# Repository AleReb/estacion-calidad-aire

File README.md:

# Estación Multiparamétrica de Calidad del Aire

La estación integra sensores **electroquímicos**, **ópticos** y **meteorológicos** en una estructura vertical compacta. El sistema recolecta, almacena y transmite datos **en tiempo casi real**, lo que permite correlacionar calidad del aire y condiciones meteorológicas. Actualmente se encuentra en construcción con pruebas de campo; todos los sensores cuentan con especificaciones validadas y se calibran antes de entrar en operación.

## Características destacadas
- Soporte tipo torre de 2–5 m con exposición 360° y altura de medición a 1,5 m sobre nivel del suelo.
- Alimentación autónoma mediante panel solar y banco de baterías.
- Comunicaciones GSM/4G complementadas con almacenamiento local en microSD.
- Plataforma única con sensores sincronizados y módulos accesibles para reemplazo rápido.
- Incluye colectores para muestreo pasivo de material particulado sedimentable (conforme a Resolución Exenta N° 1449 del MMA, 2023).

## Sensores integrados
| Tipo | Modelo | Rango / Límite | Precisión / Resolución | Tecnología |
| --- | --- | --- | --- | --- |
| PM1.0/2.5/10 | Plantower PMS5003ST | 1 µg/m³ (límite) | ±1 µg/m³ | Óptico láser |
| O₃ | Alphasense OX-B431 | 1 ppb (límite) | ±1 ppbv | Amperométrico |
| NO₂ | Alphasense NO2-B43F | 1 ppb (límite) | ±1 ppbv | Amperométrico |
| CO | Alphasense CO-B4 | 1 ppm (límite) | ±1 ppmv | Amperométrico |
| NO | Alphasense NO-B4 | 1 ppb (límite) | ±1 ppbv | Amperométrico |
| CO₂ | Winsen MH-Z19B/MH-Z19C | 1 ppm (resolución) | — | Infrarrojo NDIR |
| VOC (totales) | Winsen ZE40A-TVOC | 0–2 ppm | 0.01 ppm | PID/MOS |
| SO₂ | Alphasense SO2-B4 (objetivo) | 5 ppb (error) | — | Electroquímico |
| Meteo (T, HR, P, VV, DV, precipitación, radiación, UV, luz) | ComWinTop CWT-UWD-SDTHAPSIR / CWT-UR-S | Según ficha | Ver ficha | RS485 (Modbus) |

## Aplicaciones
- Monitoreo ciudadano y municipal.
- Validación de sensores de bajo costo.
- Correlación con estaciones de referencia.
- Evaluación de impactos urbanos o industriales.

## Guía rápida del repositorio
- `01-requisitos-interesados/`: necesidades y casos de uso basados en el brochure técnico.
- `02-requisitos-sistema/`: requisitos funcionales/no funcionales y especificaciones (contaminantes, soporte meteo, emergentes).
- `03-diseño-arquitectura/`: decisiones, vistas de arquitectura y espacio para diagramas.
- `04-diseño-detallado/`: definición preliminar de hardware, firmware y gestión de datos.
- `05-implementacion/`: árbol para hardware (PCB, carcasas, componentes), firmware (PlatformIO) y software (backend/frontend/scripts).
- `06-10/`: integración, verificación, validación, despliegue y operación/mantenimiento.
- `documentacion/`, `datos/`, `herramientas/`, `configuracion/`: repositorios para datasheets, datasets EPA/WMO, utilidades y perfiles de configuración.
- `gestion-proyecto/planificacion/roles-responsabilidades.md`: lista actualizada de cargos, incluyendo QA/QC y administración de datos.

## Índice de informes y manuales
| Recurso | Ubicación | Descripción |
| --- | --- | --- |
| Manual ISB/AFE y notas de aplicación Alphasense | [`documentacion/datasheets-sensores/sensores-gases/electroquimicos/alphasense/`](documentacion/datasheets-sensores/sensores-gases/electroquimicos/alphasense/) | PDFs AAN-803-05, manual ISB y guía rápida de placas que convierten corriente a voltaje para sensores B4/B43F. |
| Tutorial offsets WEe/AEe | [`documentacion/manuales-tecnicos/calibracion/tutorial-offsets-wee-aee.md`](documentacion/manuales-tecnicos/calibracion/tutorial-offsets-wee-aee.md) | Procedimiento paso a paso para medir offsets electrónicos en placas ISB/AFE con multímetro. |
| Nota técnica AAN-803-05 | [`documentacion/manuales-tecnicos/calibracion/AAN-803-05.pdf`](documentacion/manuales-tecnicos/calibracion/AAN-803-05.pdf) | Referencia oficial del fabricante para calibraciones electroquímicas. |
| Brochure y ficha de operación en terreno | [`documentacion/manuales-tecnicos/operacion/brochure.pdf`](documentacion/manuales-tecnicos/operacion/brochure.pdf) · [`documentacion/manuales-tecnicos/operacion/Ficha Terreno AIRE.pdf`](documentacion/manuales-tecnicos/operacion/Ficha%20Terreno%20AIRE.pdf) | Ficha de despliegue en terreno y brochure visual del proyecto. |
| Reporte laboratorio – voltaje circuito abierto ISB | [`documentacion/informes-pruebas/laboratorio/condiciones-controladas/Volt_Circuito_abierto_ISB_alphasense_est05/Voltage_circuito_abierto_alphasense_estacion_5.pdf`](documentacion/informes-pruebas/laboratorio/condiciones-controladas/Volt_Circuito_abierto_ISB_alphasense_est05/Voltage_circuito_abierto_alphasense_estacion_5.pdf) | Informe LaTeX con fotos e instrumental para medición de voltaje en placas ISB. Incluye fuentes `.tex` e imágenes en `img/`. |
| Reporte campo – co-ubicación SINCA | [`documentacion/informes-pruebas/campo/co-ubicacion-sinca/calibracion-sinca-1.pdf`](documentacion/informes-pruebas/campo/co-ubicacion-sinca/calibracion-sinca-1.pdf) | Evidencia PDF de campaña de co-ubicación para calibraciones con red SINCA. |

## Equipo de trabajo
| Rol | Responsable | Función principal |
| --- | --- | --- |
| Dirección del proyecto | Zoe Fleming | Define lineamientos estratégicos, asegura recursos y relación con interesados de alto nivel. |
| Coordinación general | Luis Gómez | Coordina disciplinas, consolida reportes de avance y comunica el estado del proyecto. |
| Firmware y comunicaciones | Alejandro Rebolledo | Lidera programación de firmware, integración de sensores y enlaces GSM/4G/RS485. |
| Operaciones en terreno | Pablo Ortiz | Gestiona despliegues de torres, logística de instalación y soporte en campo. |
| Mediciones y administración de datos | Catalina Azola | Define rutinas de muestreo, resguarda datos de mediciones y entrega datasets a QA/QC. |
| Documentación regulatoria, QA/QC y bases de datos | Christopher Silva | Mantiene cumplimiento normativo, verifica calidad de datos y gestiona respaldos/registros. |
| Diseño de hardware y componentes | Rodrigo Ortega | Diseña la estructura física, integra panel solar + baterías y define componentes mecánicos. |
| Diseño electrónico | Sebastián Adonay | Desarrolla la electrónica de adquisición y acondicionamiento para sensores electroquímicos, ópticos y meteorológicos. |

## Cómo colaborar (incluye uso con Codex)
1. Clona este repositorio y revisa el README antes de abrir Codex.
2. Abre una sesión de Codex desde la raíz (`codex run`), y revisa los archivos en `gestion-proyecto/planificacion/` para conocer roles y tareas pendientes.
3. Documenta nuevas decisiones en la carpeta correspondiente (por ejemplo, requisitos → `02-...`, hardware → `04-diseño-detallado/...`).
4. Añade contenidos reales en los documentos vacíos; si no existe información todavía, deja una nota explícita indicando que está pendiente (mantén el estilo usado hasta ahora).
5. Usa `.gitkeep` para conservar directorios vacíos si agregas nuevos subcontenidos.
6. Antes de hacer commit, ejecuta `git status` para revisar qué archivos cambiaste y organiza los mensajes de commit por área (requisitos, arquitectura, firmware, etc.).

## Contacto
Proyecto en desarrollo: **Estación Multiparamétrica de Monitoreo Ambiental**  \
Contacto: [luis.gomez@udd.cl](mailto:luis.gomez@udd.cl)

## Descargo de Responsabilidad

El código y la documentación de este proyecto se ofrecen "tal cual", sin garantías de ningún tipo, expresas o implícitas. El uso de este material es bajo su propio riesgo. Los autores no se hacen responsables de ningún daño o pérdida que pueda surgir de su uso.

## Licencia

Este proyecto está licenciado bajo la **Creative Commons Attribution-NonCommercial 4.0 International (CC BY-NC 4.0)**.

Usted es libre de:
-   **Compartir** — copiar y redistribuir el material en cualquier medio o formato.
-   **Adaptar** — remezclar, transformar y construir sobre el material.

Bajo los siguientes términos:
-   **Atribución** — Debe dar crédito de manera adecuada, proporcionar un enlace a la licencia, e indicar si se han realizado cambios.
-   **NoComercial** — No puede utilizar el material para una finalidad comercial.

Para ver una copia de esta licencia, visite [http://creativecommons.org/licenses/by-nc/4.0/](http://creativecommons.org/licenses/by-nc/4.0/) o consulte el archivo [LICENSE](LICENSE) en este repositorio.

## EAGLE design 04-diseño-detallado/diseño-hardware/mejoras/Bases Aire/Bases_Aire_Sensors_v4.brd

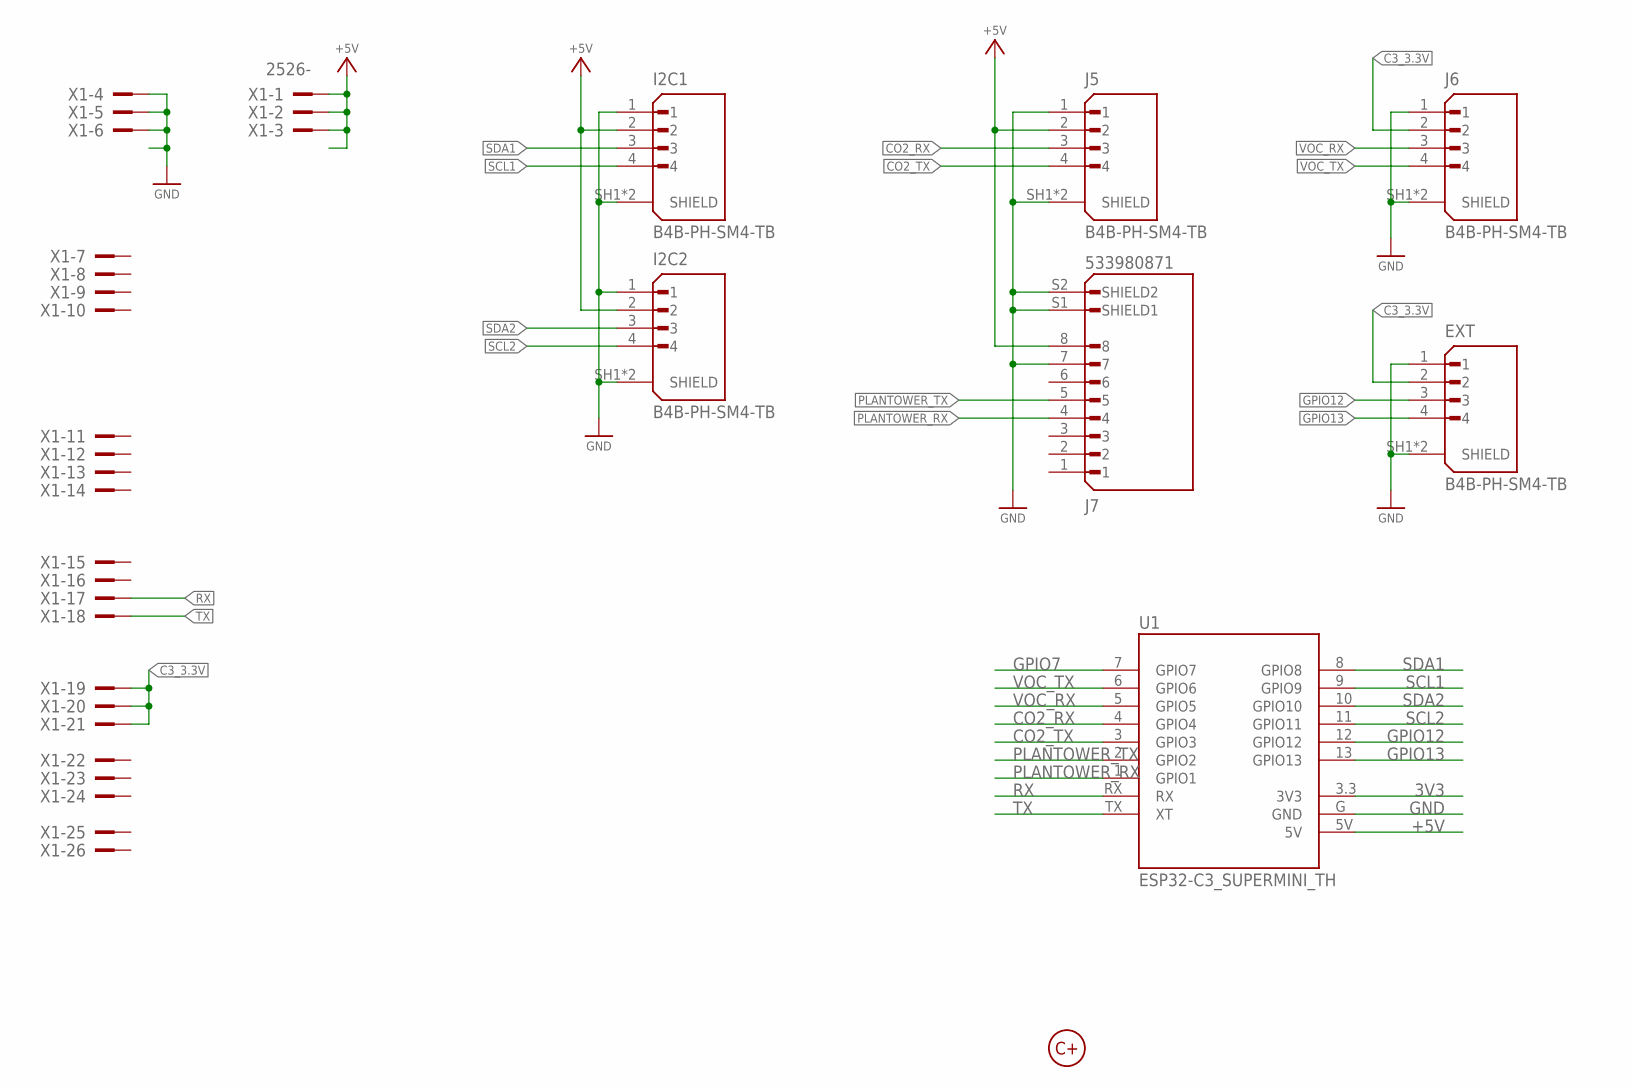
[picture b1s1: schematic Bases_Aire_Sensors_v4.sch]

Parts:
EXT: B4B-PH-SM4-TB; JST_B4B-PH-SM4-TB
I2C1, I2C2: B4B-PH-SM4-TB; JST_B4B-PH-SM4-TB
J5, J6: B4B-PH-SM4-TB; JST_B4B-PH-SM4-TB
J7: 533980871; MOLEX_533980871
U1: ESP32-C3_SUPERMINI_TH; MODULE_ESP32-C3_SUPERMINI_TH
U$1: LOGO_CMAS10MM; LOGO_10MM
X1: 2526-; PAK100/2500-26

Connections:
3V3: U1.3.3 (3V3)
+5V: I2C1.2, I2C2.2, J5.2, J7.8, U1.5V, X1.1, X1.2, X1.3
C3_3.3V: EXT.2, J6.2, X1.19, X1.20, X1.21
CO2_RX: J5.3, U1.4 (GPIO4)
CO2_TX: J5.4, U1.3 (GPIO3)
GND: EXT.1, EXT.SH1 (SHIELD), EXT.SH2 (SHIELD), I2C1.1, I2C1.SH1 (SHIELD), I2C1.SH2 (SHIELD), I2C2.1, I2C2.SH1 (SHIELD), I2C2.SH2 (SHIELD), J5.1, J5.SH1 (SHIELD), J5.SH2 (SHIELD), J6.1, J6.SH1 (SHIELD), J6.SH2 (SHIELD), J7.7, J7.S1 (SHIELD1), J7.S2 (SHIELD2), U1.G (GND), X1.4, X1.5, X1.6
GPIO7: U1.7 (GPIO7)
GPIO12: EXT.3, U1.12 (GPIO12)
GPIO13: EXT.4, U1.13 (GPIO13)
PLANTOWER_RX: J7.4, U1.1 (GPIO1)
PLANTOWER_TX: J7.5, U1.2 (GPIO2)
RX: U1.RX, X1.17
SCL1: I2C1.4, U1.9 (GPIO9)
SCL2: I2C2.4, U1.11 (GPIO11)
SDA1: I2C1.3, U1.8 (GPIO8)
SDA2: I2C2.3, U1.10 (GPIO10)
TX: U1.TX (XT), X1.18
VOC_RX: J6.3, U1.5 (GPIO5)
VOC_TX: J6.4, U1.6 (GPIO6)

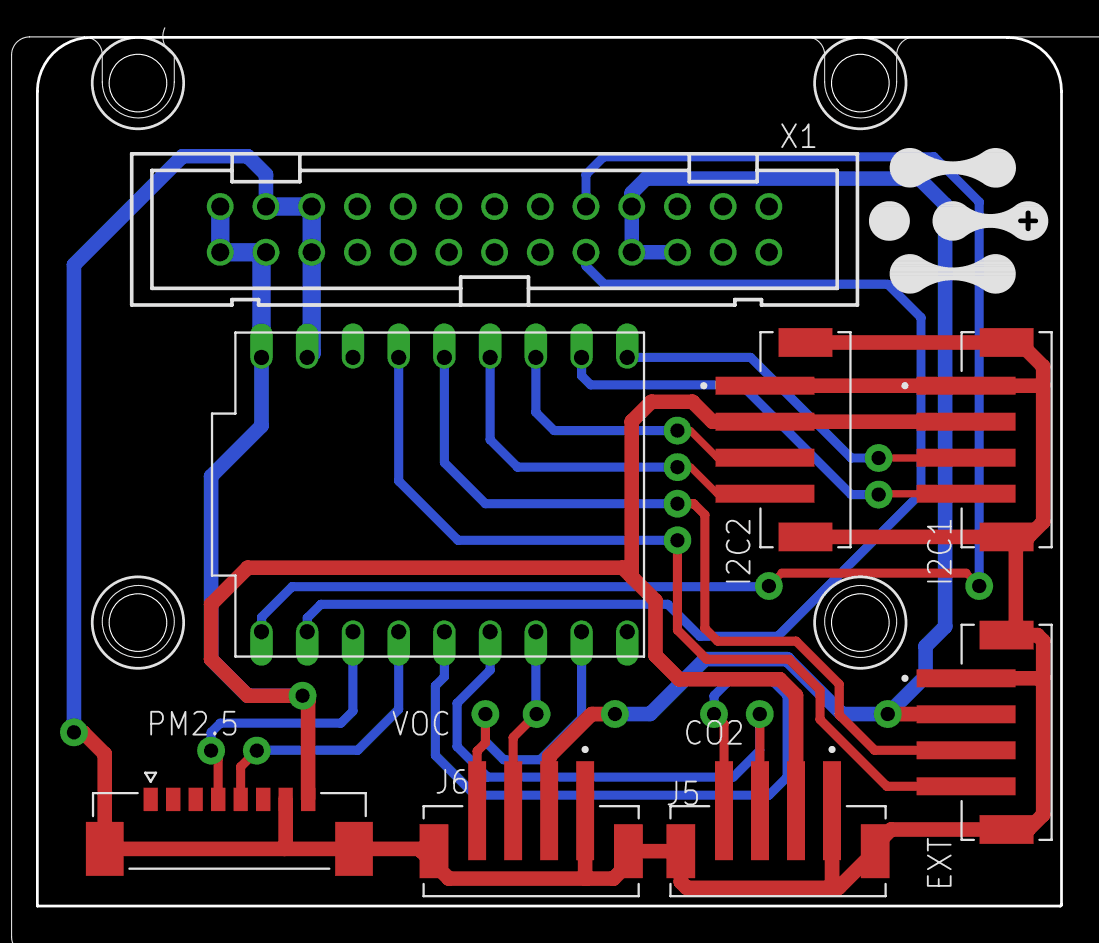
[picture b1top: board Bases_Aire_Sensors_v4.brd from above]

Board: 2 copper layers, 56.9 x 48.3 mm, 9 parts (0 on the bottom side), 17 nets.

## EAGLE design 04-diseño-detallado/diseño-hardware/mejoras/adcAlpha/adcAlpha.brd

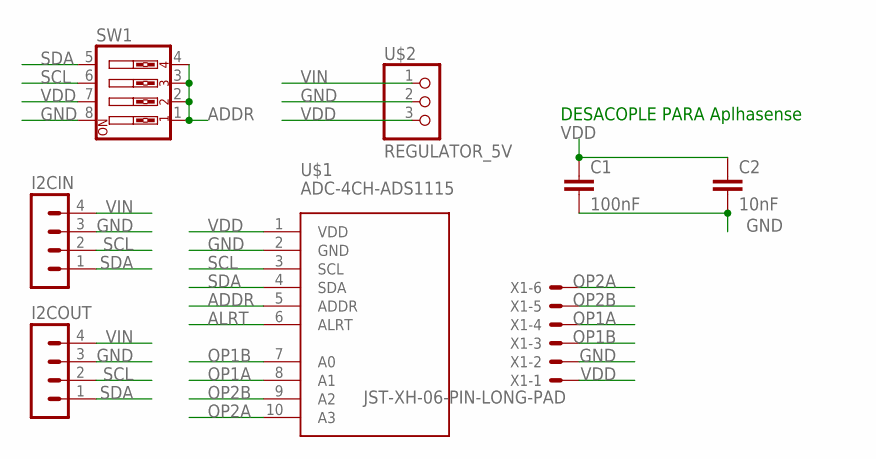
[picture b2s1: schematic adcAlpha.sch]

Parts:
C1: 100nF; CAP-PTH-SMALL-KIT
C2: 10nF; CAP-PTH-SMALL-KIT
I2CIN, I2COUT: MA04-1
SW1: SW_DIP-4; EDG-04
U$1: ADC-4CH-ADS1115
U$2: REGULATOR_5V; 1X03
X1: JST-XH-06-PIN-LONG-PAD; JST-XH-06-PACKAGE-LONG-PAD

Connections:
ADDR: SW1.1, SW1.2, SW1.3, SW1.4, U$1.5 (ADDR)
ALRT: U$1.6 (ALRT)
GND: C1.2, C2.2, I2CIN.3, I2COUT.3, SW1.8, U$1.2 (GND), U$2.2 (GND), X1.2
OP1A: U$1.8 (A1), X1.4
OP1B: U$1.7 (A0), X1.3
OP2A: U$1.10 (A3), X1.6
OP2B: U$1.9 (A2), X1.5
SCL: I2CIN.2, I2COUT.2, SW1.6, U$1.3 (SCL)
SDA: I2CIN.1, I2COUT.1, SW1.5, U$1.4 (SDA)
VDD: C1.1, C2.1, SW1.7, U$1.1 (VDD), U$2.3 (OUT5V), X1.1
VIN: I2CIN.4, I2COUT.4, U$2.1 (IN)

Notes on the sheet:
DESACOPLE PARA Aplhasense

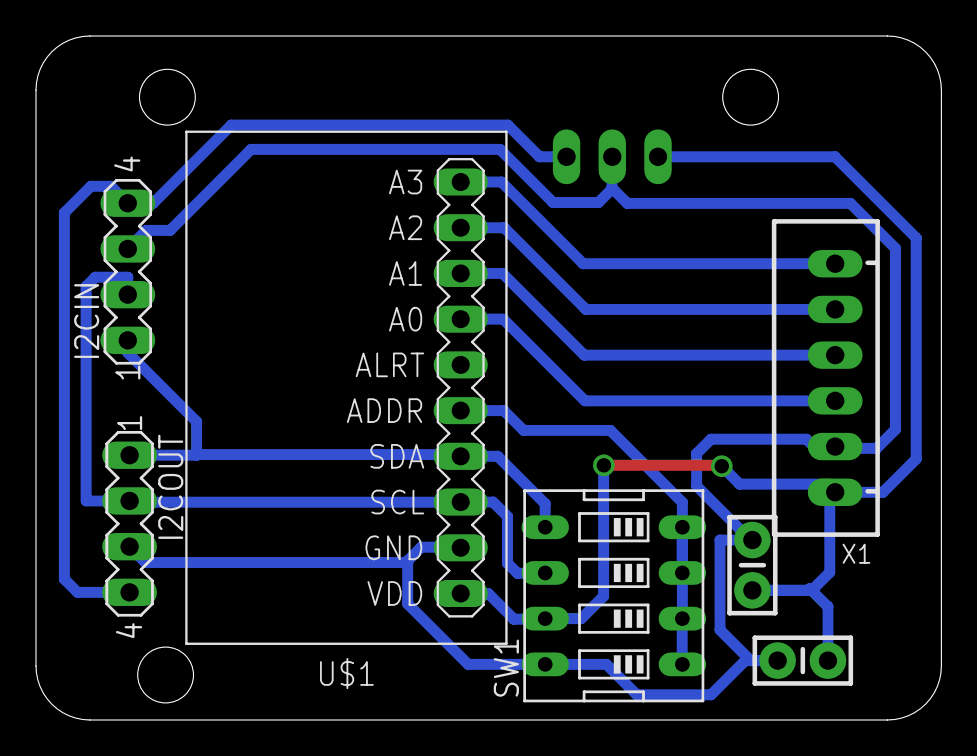
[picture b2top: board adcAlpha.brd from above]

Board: 2 copper layers, 50.3 x 38.0 mm, 8 parts (1 on the bottom side), 10 nets.

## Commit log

2025-11-11 Estructura inicial de Estación Multiparamétrica
2025-11-11 actualizacion README
2025-11-11 se crea tutorial alphasense
2025-11-11 Update roles-responsabilidades.md
    pequeño update de equipo A. R.
2025-11-13 Agregar documentación de datasheets y reportes de laboratorio
2025-11-13 se genera documento y agregan comentarios para trabajar
2025-11-17 se actualiza el manual de mdicion de ruido
2025-11-17 Actualización del documento PDF de condiciones controladas se agrega archivo de latex y pdf recomendaciones de mejoras en hardwar diseño
2025-11-17 Add detailed documentation for high PSRR regulators and high-resolution ADCs for Alphasense gas sensors
    - Introduced a comprehensive LaTeX document outlining suitable linear regulators with high PSRR and low noise characteristics for powering Alphasense gas sensors.
    - Included specifications and pricing for various regulators such as Microchip MCP1754, Diodes Inc. AP7387, STMicroelectronics LDO40L, TI TPS7A4700, and Analog Devices LT3042.
    - Added a section on high-resolution ADCs (I²C/SPI) suitable for reading low-amplitude signals from Alphasense sensors, featuring options like Texas Instruments ADS1115, Microchip MCP3424, and TI/Wav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
    - Provided references and links to datash
2025-11-17 Add files via upload
    se sube ultimo codigo , no hay mejoras previstas hasta hacer mas pruebas
2025-11-17 Add initial README.md for Firmware Placa Madre Línea Base v0.0.3 with project overview and features
2025-11-17 Add LICENSE file with copyright and licensing information
2025-12-29 se sube pcb del adc directo al sensor
2026-01-13 se sube pcb colector de señales actualizado

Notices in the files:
parts and their libraries:
diy-modules: Released under the Creative Commons Attribution 4.0 International License: http://creativecommons.org/licenses/by/4.0
SparkFun-Capacitors: Licensing: Creative Commons ShareAlike 4.0 International - https://creativecommons.org/licenses/by-sa/4.0
